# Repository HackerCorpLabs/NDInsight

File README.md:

# NDInsight - Norsk Data Computer Systems Analysis & Documentation

**Comprehensive technical analysis and documentation for Norsk Data computer systems**

---

## 📖 Overview

**NDInsight** is a centralized repository of deep technical analysis, reverse-engineered documentation, OCR'd manuals, and implementation guides for **Norsk Data computer systems** - NORD-1/10/50, ND-100/110/120, ND-500 and ND-5000 - focusing on the **SINTRAN III operating system** and its hardware architecture.

The analysis is made from original SINTRAN III source code, official Norsk Data technical manuals, and with heavy use of AI (Claude AI, Cursor AI, ChatGPT AI). While comprehensive, there might be errors and hallucinations - use with appropriate verification.

### What's Inside

- **SINTRAN III NPL source code** - 45 files of authentic operating system source code, plus symbol tables
- **Kernel-level documentation** extracted from SINTRAN III source code
- **Hardware analysis** of communication protocols (HDLC, X.21, X.25, TAD, XMSG, Octobus)
- **ND-500 / ND-5000 coprocessor** integration and communication, reverse-engineered end to end
- **Device driver** implementation details (SCSI, DOMINO/NUCLEUS, printers) with complete source code
- **Emulator implementation** guides and production C# code
- **Hundreds of official Norsk Data reference manuals and product data sheets**, OCR'd and indexed
- **A hands-on reverse-engineering toolkit** (segment carver + boot-floppy analysis) with real source, disassembly and carved evidence

---

## 🗂️ Repository Structure

```
NDInsight/
├── README.md                    ← You are here
├── CLAUDE.md                    ← AI assistant guidance
├── MERMAID_COLOR_STANDARDS.md   ← Diagram color standards
├── Developer/                   ← Developer guides and language references
├── Installation/                ← Installing SINTRAN III and application software
│   ├── OS/                      ← Installing SINTRAN III from distribution floppies
│   ├── Communication/           ← Installing COSMOS/Ethernet/TCP-IP/X.21/X.25 products
│   ├── Software/                ← Installing application software (later phase)
│   ├── OWS/                     ← Office Work Station: WinLink/WinPrint/WinSMX, PC-NOTIS, SPRINT printing, SIBAS/R
│   ├── Installation-Description/← OCR'd "Program Description" install/requirements sheets
│   └── Product-Info/            ← OCR'd product data-sheets/brochures
├── Operations/                  ← Operator and user guides (COSMOS, SINTRAN)
├── Reference-Manuals/           ← Official Norsk Data reference manuals (incl. NORD-1, NORD-10, ND-500/5000, NOTIS)
├── scripts/                     ← Documentation processing scripts (Python, PowerShell)
├── tools/                       ← Reverse-engineering toolkit
│   ├── sintran-segment-carver/  ← Carved SINTRAN image segments, symbol matching, RE notes
│   └── boot-floppy/             ← Disc boot-sector anatomy, MACM generation, patch analysis
└── SINTRAN/                     ← SINTRAN III Operating System
    ├── Devices/                 ← Hardware device documentation (HDLC, SCSI, DOMINO/NUCLEUS)
    ├── Emulator/                ← C# emulator implementation guides
    ├── File-Formats/            ← On-disk / on-tape file format analysis
    ├── Filesystem/              ← SINTRAN filesystem structures
    ├── ND500/                   ← ND-500 coprocessor documentation
    ├── ND5000/                  ← ND-5000 / Octobus documentation
    ├── NPL-SOURCE/              ← ⭐ SINTRAN III source code & symbols
    ├── OS/                      ← Core OS kernel documentation
    ├── Print/                   ← Printing/spooling subsystem
    ├── Release-Documentation/   ← SINTRAN III release notes (versions J-N)
    ├── SINTRAN Structures/      ← System structures and data analysis
    ├── TAD/                     ← TAD protocol analysis
    ├── TSS/                     ← TSS subsystem documentation
    └── XMSG/                    ← XMSG message system: DOC/ (protocol, API, commands), SRC/ (C# library), constants
```

---

## 🚀 Quick Start

### New to SINTRAN III?

**Start with these documents:**
1. [SINTRAN/OS/00-SINTRAN-ARCHITECTURE-OVERVIEW.md](SINTRAN/OS/00-SINTRAN-ARCHITECTURE-OVERVIEW.md) - System overview
2. [SINTRAN/OS/01-BOOT-SEQUENCE.md](SINTRAN/OS/01-BOOT-SEQUENCE.md) - How the system boots
3. [SINTRAN/README.md](SINTRAN/README.md) - Complete SINTRAN documentation guide

### Installing a System?

**Start here:**
1. [Installation/README.md](Installation/README.md) - Installation guides index
2. [Installation/OS/](Installation/OS/) - Installing SINTRAN III from distribution floppies
3. [Installation/Installation-Description/README.md](Installation/Installation-Description/README.md) - Per-product install/requirements sheets

### Building an Emulator?

**Critical resources:**
1. [SINTRAN/NPL-SOURCE/README.md](SINTRAN/NPL-SOURCE/README.md) - Access to actual source code
2. [SINTRAN/Emulator/README.md](SINTRAN/Emulator/README.md) - C# implementation guides
3. [SINTRAN/OS/19-MEMORY-MAP-REFERENCE.md](SINTRAN/OS/19-MEMORY-MAP-REFERENCE.md) - Memory layout

### Developing Software?

**Language guides:**
1. [Developer/README.md](Developer/README.md) - Developer documentation index
2. [Reference-Manuals/README.md](Reference-Manuals/README.md) - Complete language references

### Reverse-Engineering a SINTRAN Image?

**Toolkit and method:**
1. [tools/sintran-segment-carver/](tools/sintran-segment-carver/) - Carved segments, symbol matching, byte-verified findings
2. [tools/boot-floppy/](tools/boot-floppy/) - Disc boot-sector anatomy, MACM generation dialogue, patch format

---

## 📂 Main Sections

Each top-level folder has its own README with full navigation; this page only summarizes.

| Section | Contents | Index |
|---|---|---|
| **[Developer/](Developer/)** | Language guides (NPL, MAC, PLANC, PASCAL, FORTRAN, COBOL, BASIC, C), editors (QED, PED, LED), build workflow | [README.md](Developer/README.md) |
| **[Installation/](Installation/)** | How to install SINTRAN III and applications; OCR'd install-description and product-info sheets; the [OWS/](Installation/OWS/README.md) office-workstation family | [README.md](Installation/README.md) |
| **[Operations/](Operations/)** | Operator/admin guides for COSMOS networking and SINTRAN system operation | [README.md](Operations/README.md) |
| **[Reference-Manuals/](Reference-Manuals/)** | Official Norsk Data reference manuals across the whole product line - CPU architecture, assemblers, languages, editors, NOTIS office suite, NORD-1/NORD-10 | [README.md](Reference-Manuals/README.md) |
| **[SINTRAN/](SINTRAN/)** | The core: kernel docs, source code, device drivers, ND-500/ND-5000 integration, protocols, emulator | [README.md](SINTRAN/README.md) |
| **[tools/](tools/)** | Reverse-engineering toolkit: SINTRAN segment carver and boot-floppy/disc-generation analysis, with real source and carved evidence | [tools/README.md](tools/README.md) |

### [SINTRAN/](SINTRAN/) - Operating System Documentation

The largest and oldest part of the repository.

| Directory | Description |
|-----------|-------------|
| **[NPL-SOURCE/](SINTRAN/NPL-SOURCE/)** ⭐ | **SINTRAN III source code** - 45 NPL files + symbol tables from the s3vs-4 build |
| **[OS/](SINTRAN/OS/)** | Core kernel documentation, chapters 00-19 |
| **[Release-Documentation/](SINTRAN/Release-Documentation/)** | SINTRAN III release notes, versions J-N |
| **[SINTRAN Structures/](SINTRAN/SINTRAN%20Structures/)** | Kernel data structures analysis |
| **[Devices/](SINTRAN/Devices/)** | HDLC, SCSI and DOMINO/NUCLEUS device drivers |
| **[Emulator/](SINTRAN/Emulator/)** | C# emulator implementation guides and production code |
| **[ND500/](SINTRAN/ND500/)** | ND-500 coprocessor. ND-100 <-> ND-500 interface reverse-engineered end to end (byte-verified from L07); status of record: `SINTRAN/ND500/ND500-STATUS-AND-INDEX.md` |
| **[ND5000/](SINTRAN/ND5000/)** | ND-5000 / Octobus fabric analysis |
| **[TAD/](SINTRAN/TAD/)** | Terminal Access Device protocol |
| **[XMSG/](SINTRAN/XMSG/)** | Inter-node messaging: wire protocol, monitor-call API, C# library |
| **[Print/](SINTRAN/Print/)** | Printing/spooling subsystem |
| **[Filesystem/](SINTRAN/Filesystem/)**, **[File-Formats/](SINTRAN/File-Formats/)** | On-disk structures and file formats |
| **[TSS/](SINTRAN/TSS/)** | TSS subsystem |

📖 **[See SINTRAN/README.md for the complete overview](SINTRAN/README.md)**

---

## 📊 Repository Statistics

*Counts are approximate and drift as the repository grows - see each section's own README for exact current numbers.*

| Section | Markdown Files | Size | Highlights |
|---|---|---|---|
| **SINTRAN/** | ~550 | ~92MB | NPL source (45 files), kernel docs (ch. 00-19), ND-500/5000, XMSG, TSS |
| **tools/** | ~400 | ~200MB | Segment carver + boot-floppy RE toolkit; also 250+ carved binaries, 200+ C/ASM/NPL source files |
| **Installation/** | ~700 | ~21MB | 284 OCR'd install-description sheets + 364 OCR'd product-info sheets + install guides |
| **Reference-Manuals/** | ~160 | ~29MB | Official manuals: NORD-1, NORD-10, ND-500/5000, NOTIS suite, languages, editors |
| **Developer/** | ~35 | ~4MB | Language guides, editors, build workflow |
| **Operations/** | ~20 | ~3MB | COSMOS and SINTRAN operator guides |
| **Total** | **~1,900** | **~350MB** | - |

### Source Code Coverage

**What We Have (NPL Source):**
- ✅ Kernel/Monitor core (MON60)
- ✅ SCSI, DOMINO/NUCLEUS and HDLC device drivers
- ✅ ND-500 interface code
- ✅ Disk I/O subsystem
- ✅ Segment administration
- ✅ HASP protocol
- ✅ Terminal handlers (partial)

**What's Missing:**
- ❌ Complete file system implementation (symbols available)
- ❌ Complete XMSG message system source (symbols + wire protocol available)
- ❌ Complete terminal handlers
- ❌ Network subsystems beyond HDLC/XMSG/Octobus
- ❌ Batch processing components

---

## 🛠️ Technologies Documented

### Hardware
- **NORD-1, NORD-10/10-S, NORD-50** - Early Norsk Data minicomputers
- **ND-100/110/120** - 16-bit minicomputer family (1970s-1990s)
- **ND-500 / ND-5000** - 32-bit coprocessor / server family
- **MPM5** - Multiport memory (shared RAM)
- **Octobus** - ND-100 <-> ND-5000 fabric
- **COM5025** - HDLC controller chip
- **NCR 5386** - SCSI protocol controller

### Software
- **SINTRAN III** - Real-time operating system
- **NPL** - NORD Programming Language (system programming)
- **MAC** - Macro assembler
- **PLANC, PASCAL, FORTRAN, COBOL, BASIC, C, SIMULA, Ada** - Application languages
- **NOTIS** - Norsk Data's office automation suite (WP, DS, IR, ID, RG, CALC, BG, DRAW, PM)

### Protocols
- **HDLC / X.21 / X.25 / LAPB** - Link and packet layers
- **XMSG** - Inter-node messaging (SINTRAN's native IPC/networking layer)
- **COSMOS** - Norsk Data's network operating environment
- **TAD** - Terminal Access Device protocol

---

## 🎓 Documentation Methodology

### Sources
1. **SINTRAN III Source Code** - Direct NPL source analysis (s3vs-4 build)
2. **Official Norsk Data Manuals** - OCR'd from scanned originals (see Acknowledgments)
3. **Protocol Specifications** - HDLC, X.21, X.25, TAD standards
4. **Reverse Engineering** - Bit-level / byte-verified analysis when source isn't available

### Quality Standards
- ✅ **No guesswork** - Only verified facts from source/manuals; unverified claims are marked `ASSUMPTION:` or `UNVERIFIED:`
- ✅ **Source citations** - Every claim traced to source
- ✅ **Cross-references** - Extensive linking between documents
- ✅ **Visual aids** - Mermaid diagrams for complex flows
- ✅ **Production code** - Working C# implementations included
- ✅ **WCAG 2.1 AA** - Accessible diagram color standards

---

## 🚀 Use Cases

### For Emulator Developers
→ Start at [SINTRAN/Emulator/README.md](SINTRAN/Emulator/README.md)
- Understand SINTRAN kernel internals
- Implement accurate hardware emulation
- Access production C# code
- Verify against actual NPL source

### For System Archaeologists / Reverse Engineers
→ Start at [tools/sintran-segment-carver/](tools/sintran-segment-carver/) and [SINTRAN/OS/README.md](SINTRAN/OS/README.md)
- Study 1970s-1980s OS design
- Carve and cross-reference SINTRAN image segments
- Analyze interrupt-driven architecture, paging and multi-CPU coordination

### For Software Developers
→ Start at [Developer/README.md](Developer/README.md)
- Learn SINTRAN development
- Choose your language (8+ languages supported)
- Access complete reference manuals

### For System Installers / Operators
→ Start at [Installation/README.md](Installation/README.md)
- Install SINTRAN III from distribution media
- Look up a product's requirements/prerequisites
- Follow operator guides for COSMOS and SINTRAN administration

### For Hardware Analysts
→ Start at [SINTRAN/Devices/README.md](SINTRAN/Devices/README.md)
- Understand device driver architecture
- Analyze communication protocols
- Study HDLC, SCSI and DOMINO/NUCLEUS implementations

---

## 🤝 Contributing

This repository is a work in progress. Areas for contribution:
- Additional SINTRAN subsystem analysis
- Emulator bug fixes and improvements
- Protocol trace analysis
- Hardware documentation
- Historical information and context

---

## 📜 License

**Documentation**: Creative Commons Attribution 4.0 International (CC BY 4.0)
**Code**: MIT License

---

## 🙏 Acknowledgments

- **Norsk Data AS** - Original SINTRAN III development (1970s-1980s)
- **SINTRAN Source Code** - Foundation for this analysis
- **Hardware Manuals** - Official Norsk Data documentation
- **Emulator Community** - Keeping vintage computing alive
- **Jonny Oddene** ([sintran.com](https://sintran.com/) / [norsk-data.com](http://norsk-data.com/)) - A huge thank-you for the enormous personal effort scanning and preserving thousands of Norsk Data documents. A number of the manuals in this repository were OCR'd from material sourced through his sites. Without his work to rescue and archive this documentation, a large part of it would have been lost.
- **[ndwiki.org](https://www.ndwiki.org/)** - The only wiki dedicated to Norsk Data history and technology

---

**Last Updated**: 2026-07-20

---

*Preserving the legacy of Norsk Data computing through comprehensive technical analysis and documentation.*

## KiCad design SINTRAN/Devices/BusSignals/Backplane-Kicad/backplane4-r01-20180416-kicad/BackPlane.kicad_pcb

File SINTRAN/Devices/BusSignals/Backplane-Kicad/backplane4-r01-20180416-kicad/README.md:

# ECB Backplane-4 - KiCad Project Files

**The RetroBrew Computers "ECB Backplane-4" KiCad project, revision r01 (2018-04-16), extracted from [../backplane4-r01-20180416-kicad.zip](../README.md).**

---

## Files

| File | Contents |
|------|----------|
| `BackPlane.pro` | KiCad project file |
| `BackPlane.sch` | Schematic |
| `BackPlane.kicad_pcb` | PCB layout |
| `BackPlane.net` | Netlist |
| `BackPlane.cmp` | Component-to-footprint assignment file |
| `BackPlane-cache.lib` / `BackPlane-rescue.lib` | Schematic symbol cache / rescue libraries |
| `fp-lib-table` | Footprint library table (registers `special.pretty`) |
| `Backplane-4.png` | Rendered image of the board |
| [special.pretty/](special.pretty/README.md) | Project-local footprint library |

---

**Parent:** [../README.md](../README.md)

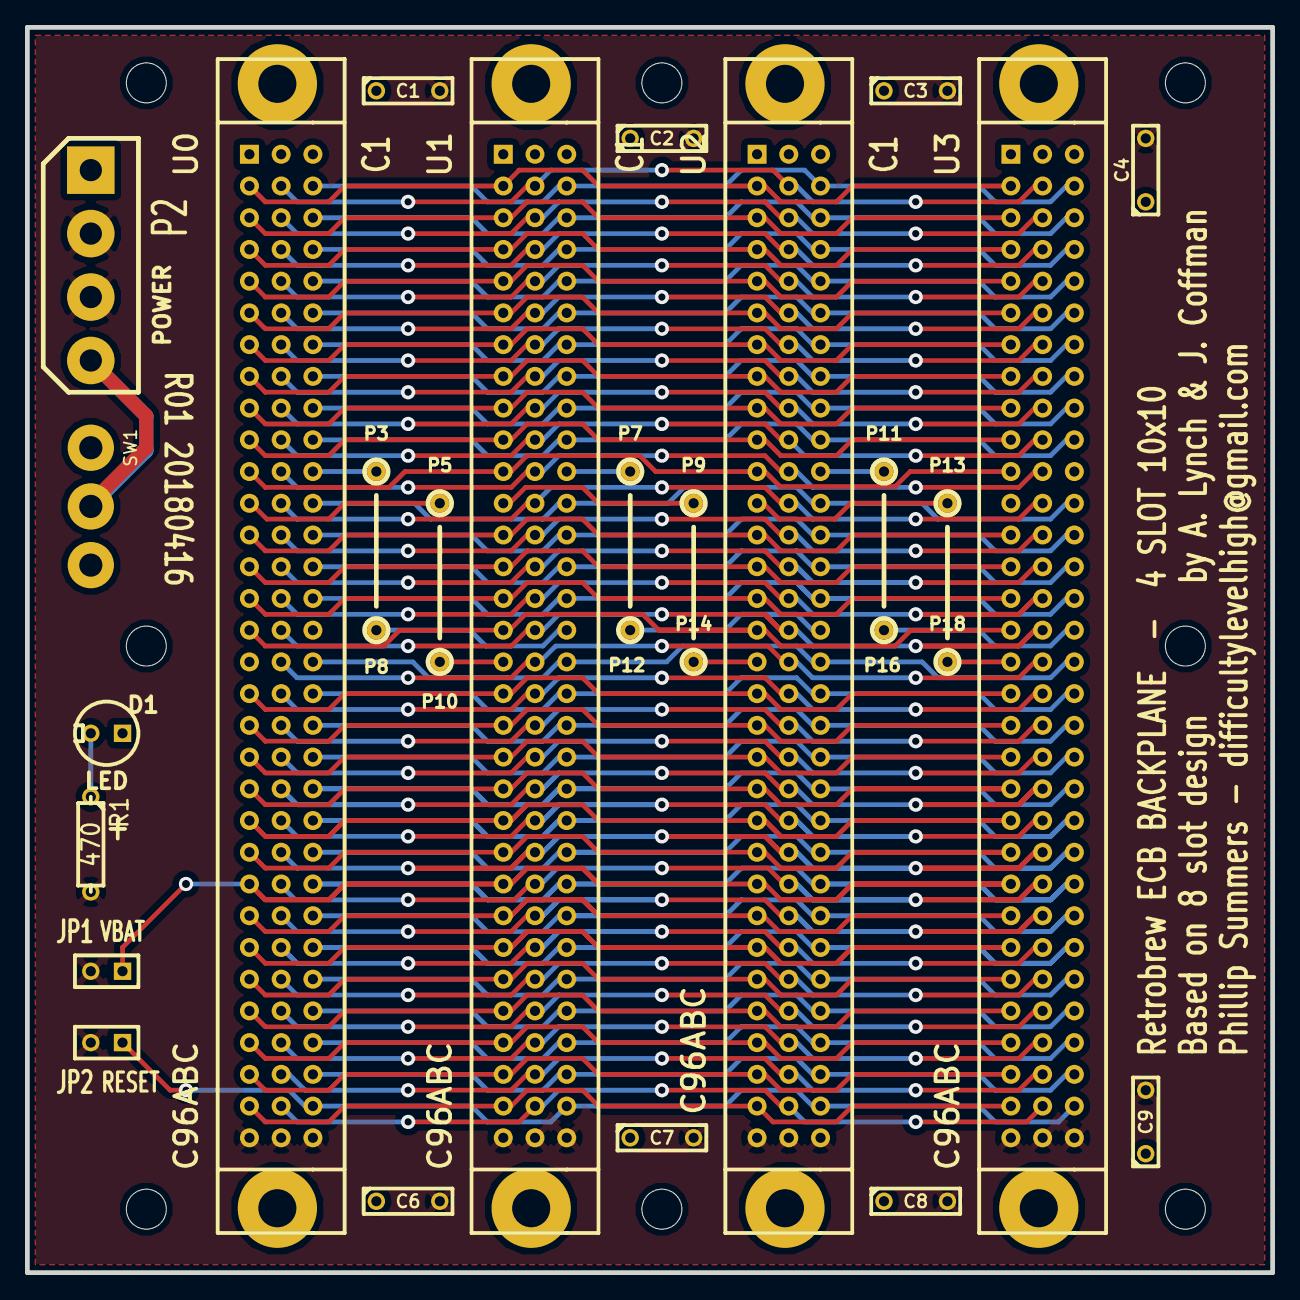
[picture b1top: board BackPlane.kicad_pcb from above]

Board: 2 copper layers, 99.7 x 99.7 mm, 30 parts (0 on the bottom side), 102 nets.

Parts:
C1, C2, C3, C4, C6, C7, C8, C9: 0.1_uF; C2
D1: LED; LEDV
JP1: VBAT; SIL-2
JP2: RESET; SIL-2
P2: POWER; bornier4
P3, P5, P7, P8, P9, P10, P11, P12, P13, P14, P16, P18: CONN_1; 0pin
R1: 470; R3
SW1: POWER; Switch-SPST-0.185
U0, U1, U2, U3: C96ABC; C96ABCFD-jrc

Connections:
//BAI0: P5.1, U0.A12
//BAI1: P9.1, U1.A12
//BAI2: P13.1, U2.A12
//BAO1: P10.1, U1.A17
//BAO2: P14.1, U2.A17
//BAO3: P18.1, U3.A17
//IEI0: P3.1, U0.C11
//IEI1: P7.1, U1.C11
//IEI2: P11.1, U2.C11
//IEO1: P8.1, U1.C16
//IEO2: P12.1, U2.C16
//IEO3: P16.1, U3.C16
/B_/BUSAK: U0.A31, U1.A31, U2.A31, U3.A31
/B_/BUSRQ: U0.A11, U1.A11, U2.A11, U3.A11
/B_/HALT: U0.C25, U1.C25, U2.C25, U3.C25
/B_/INT: U0.C21, U1.C21, U2.C21, U3.C21
/B_/IORQ: U0.A27, U1.A27, U2.A27, U3.A27
/B_/M1: U0.A20, U1.A20, U2.A20, U3.A20
/B_/MREQ: U0.C30, U1.C30, U2.C30, U3.C30
/B_/NMI: U0.C20, U1.C20, U2.C20, U3.C20
/B_/RD: U0.C24, U1.C24, U2.C24, U3.C24
/B_/RESET: JP2.1, U0.C31, U1.C31, U2.C31, U3.C31
/B_/RFSH: U0.A28, U1.A28, U2.A28, U3.A28
/B_/WAIT: U0.A10, U1.A10, U2.A10, U3.A10
/B_/WR: U0.C22, U1.C22, U2.C22, U3.C22
/B_A0: U0.C5, U1.C5, U2.C5, U3.C5
/B_A1: U0.C7, U1.C7, U2.C7, U3.C7
/B_A2: U0.A6, U1.A6, U2.A6, U3.A6
/B_A3: U0.C6, U1.C6, U2.C6, U3.C6
/B_A4: U0.A7, U1.A7, U2.A7, U3.A7
/B_A5: U0.A8, U1.A8, U2.A8, U3.A8
/B_A6: U0.A9, U1.A9, U2.A9, U3.A9
/B_A7: U0.C9, U1.C9, U2.C9, U3.C9
/B_A8: U0.C8, U1.C8, U2.C8, U3.C8
/B_A9: U0.A30, U1.A30, U2.A30, U3.A30
/B_A10: U0.C18, U1.C18, U2.C18, U3.C18
/B_A11: U0.C17, U1.C17, U2.C17, U3.C17
/B_A12: U0.C27, U1.C27, U2.C27, U3.C27
/B_A13: U0.A29, U1.A29, U2.A29, U3.A29
/B_A14: U0.A18, U1.A18, U2.A18, U3.A18
/B_A15: U0.C28, U1.C28, U2.C28, U3.C28
/B_A20: U0.B2, U1.B2, U2.B2, U3.B2
/B_A21: U0.B3, U1.B3, U2.B3, U3.B3
/B_A22: U0.B4, U1.B4, U2.B4, U3.B4
/B_A23: U0.B5, U1.B5, U2.B5, U3.B5
/B_D0: U0.C2, U1.C2, U2.C2, U3.C2
/B_D1: U0.C14, U1.C14, U2.C14, U3.C14
/B_D2: U0.C4, U1.C4, U2.C4, U3.C4
/B_D3: U0.A4, U1.A4, U2.A4, U3.A4
/B_D4: U0.A5, U1.A5, U2.A5, U3.A5
/B_D5: U0.A2, U1.A2, U2.A2, U3.A2
/B_D6: U0.A3, U1.A3, U2.A3, U3.A3
/B_D7: U0.C3, U1.C3, U2.C3, U3.C3
/B_D8: U0.B6, U1.B6, U2.B6, U3.B6
/B_D9: U0.B7, U1.B7, U2.B7, U3.B7
/B_D10: U0.B8, U1.B8, U2.B8, U3.B8
/B_D11: U0.B9, U1.B9, U2.B9, U3.B9
/B_D12: U0.B10, U1.B10, U2.B10, U3.B10
/B_D13: U0.B11, U1.B11, U2.B11, U3.B11
/B_D14: U0.B12, U1.B12, U2.B12, U3.B12
/B_D15: U0.B13, U1.B13, U2.B13, U3.B13
/B_DS0: U0.B28, U1.B28, U2.B28, U3.B28
/B_DS1: U0.B29, U1.B29, U2.B29, U3.B29
/B_IORC: U0.B24, U1.B24, U2.B24, U3.B24
/B_IOWR: U0.B22, U1.B22, U2.B22, U3.B22
/B_IRQ0: U0.B21, U1.B21, U2.B21, U3.B21
/B_IRQ1: U0.B20, U1.B20, U2.B20, U3.B20
/B_IRQ2: U0.B19, U1.B19, U2.B19, U3.B19
/B_IRQ3: U0.B18, U1.B18, U2.B18, U3.B18
/B_IRQ4: U0.B17, U1.B17, U2.B17, U3.B17
/B_IRQ5: U0.B16, U1.B16, U2.B16, U3.B16
/B_IRQ6: U0.B15, U1.B15, U2.B15, U3.B15
/B_IRQ7: U0.B14, U1.B14, U2.B14, U3.B14
/B_LOCK: U0.B31, U1.B31, U2.B31, U3.B31
/B_MRDC: U0.B25, U1.B25, U2.B25, U3.B25
/B_MWRC: U0.B27, U1.B27, U2.B27, U3.B27
/B_OFF: U0.B30, U1.B30, U2.B30, U3.B30
/NC_A13: U0.A13, U1.A13, U2.A13, U3.A13
/NC_A14: U0.A14, U1.A14, U2.A14, U3.A14
/NC_A15: U0.A15, U1.A15, U2.A15, U3.A15
/NC_A16: U0.A16, U1.A16, U2.A16, U3.A16
/NC_A19: U0.A19, U1.A19, U2.A19, U3.A19
/NC_A21: U0.A21, U1.A21, U2.A21, U3.A21
/NC_A22: U0.A22, U1.A22, U2.A22, U3.A22
/NC_A23: U0.A23, U1.A23, U2.A23, U3.A23
/NC_A24: JP1.1, U0.A24, U1.A24, U2.A24, U3.A24
/NC_A25: U0.A25, U1.A25, U2.A25, U3.A25
/NC_A26: U0.A26, U1.A26, U2.A26, U3.A26
/NC_B23: U0.B23, U1.B23, U2.B23, U3.B23
/NC_B26: U0.B26, U1.B26, U2.B26, U3.B26
/NC_C10: U0.C10, U1.C10, U2.C10, U3.C10
/NC_C12: U0.C12, U1.C12, U2.C12, U3.C12
/NC_C13: U0.C13, U1.C13, U2.C13, U3.C13
/NC_C15: U0.C15, U1.C15, U2.C15, U3.C15
/NC_C19: U0.C19, U1.C19, U2.C19, U3.C19
/NC_C23: U0.C23, U1.C23, U2.C23, U3.C23
/NC_C26: U0.C26, U1.C26, U2.C26, U3.C26
/NC_C29: U0.C29, U1.C29, U2.C29, U3.C29
/SW_VCC: C1.1, C2.1, C3.1, C4.1, C6.1, C7.1, C8.1, C9.1, D1.1, SW1.1, U0.A1, U0.B1, U0.C1, U1.A1, U1.B1, U1.C1, U2.A1, U2.B1, U2.C1, U3.A1, U3.B1, U3.C1
GND: C1.2, C2.2, C3.2, C4.2, C6.2, C7.2, C8.2, C9.2, JP1.2, JP2.2, P2.2, P2.3, R1.2, U0.A32, U0.B32, U0.C32, U1.A32, U1.B32, U1.C32, U2.A32, U2.B32, U2.C32, U3.A32, U3.B32, U3.C32
unnamed: D1.2, R1.1
VCC: P2.4, SW1.2
